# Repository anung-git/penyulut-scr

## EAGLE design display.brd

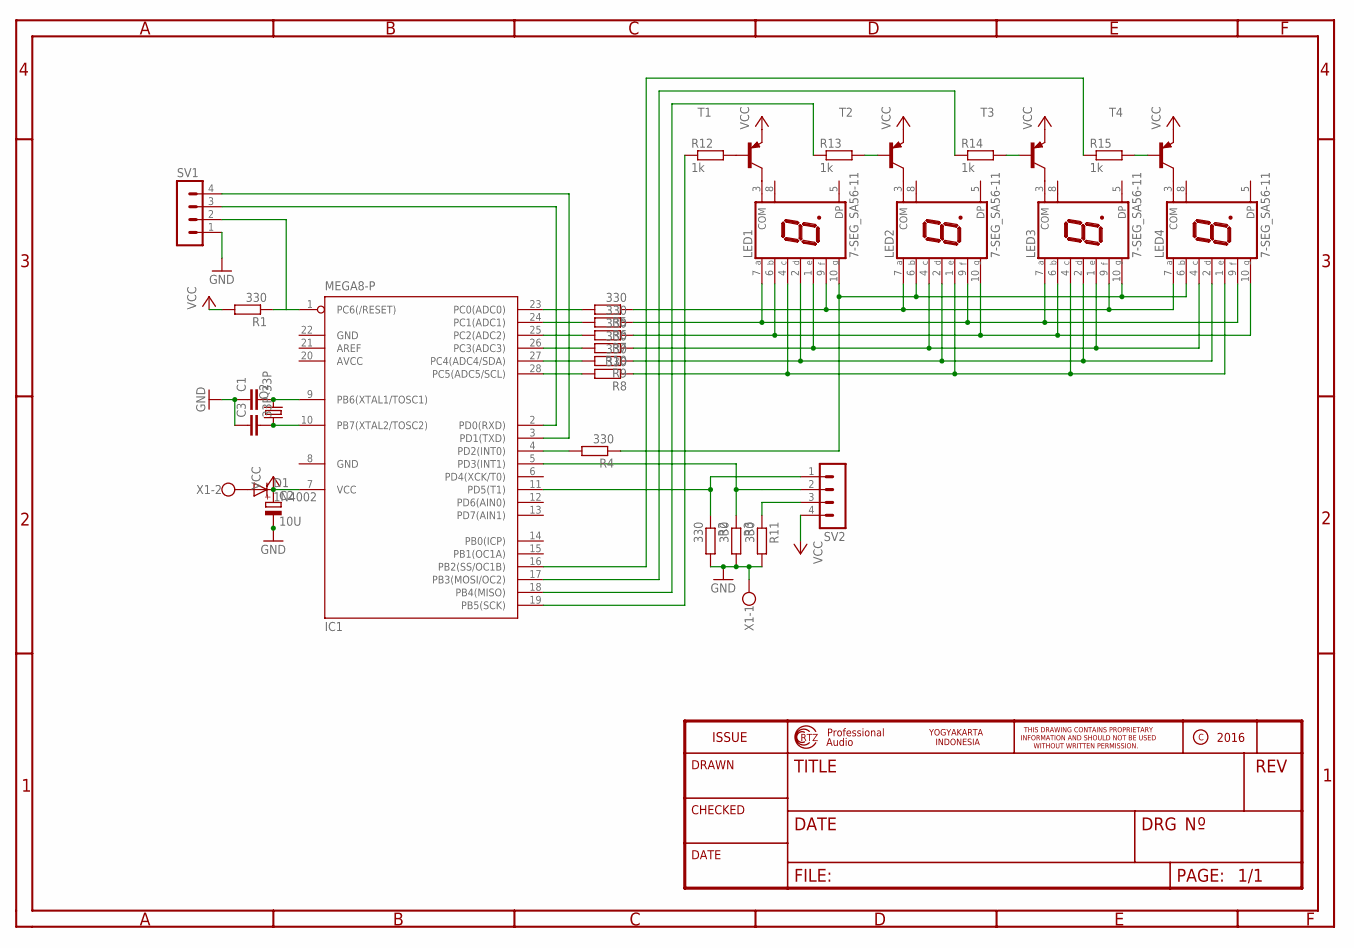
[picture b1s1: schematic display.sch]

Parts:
C1, C3: 33P; C025-025X050
C2: 10U; E2,5-6E
D1: 1N4002; DO35-10
IC1: MEGA8-P; DIL28-3
LED1, LED2, LED3, LED4: 7-SEG_SA56-11; SA56-11
Q2: CRYSTALHC49S; HC49/S
R1, R2, R3, R4, R5, R6, R7, R8, R9, R10, R11: 330; 0207/7
R12, R13, R14, R15: 1k; 0207/7
SV1, SV2: MA04-1
T1, T2, T3, T4: BC558A-PNP-TO92-EBC; TO92-EBC
X1: W237-102

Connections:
AVCC: IC1.20 (AVCC)
GND: C1.1, C2.-, C3.1, IC1.8 (GND), IC1.22 (GND), R2.2, R3.2, R11.2, SV1.1, X1.1
unnamed: IC1.23 (PC0(ADC0)), R5.2
unnamed: LED1.7 (A), LED2.9 (F), LED3.7 (A), LED4.9 (F), R6.1
unnamed: LED1.1 (E), LED2.4 (C), LED3.1 (E), LED4.4 (C), R10.1
unnamed: LED1.2 (D), LED2.2 (D), LED3.2 (D), LED4.2 (D), R9.1
unnamed: LED1.6 (B), LED2.10 (G), LED3.6 (B), LED4.10 (G), R7.1
unnamed: LED1.3 (COM), T1.C
unnamed: LED2.3 (COM), T2.C
unnamed: LED1.4 (C), LED2.1 (E), LED3.4 (C), LED4.1 (E), R8.1
unnamed: C1.2, IC1.9 (PB6(XTAL1/TOSC1)), Q2.2
unnamed: C3.2, IC1.10 (PB7(XTAL2/TOSC2)), Q2.1
unnamed: IC1.2 (PD0(RXD)), SV1.3
unnamed: IC1.24 (PC1(ADC1)), R6.2
unnamed: IC1.1 (PC6(/RESET)), R1.1, SV1.2
unnamed: LED3.3 (COM), T3.C
unnamed: LED4.3 (COM), T4.C
unnamed: IC1.25 (PC2(ADC2)), R7.2
unnamed: IC1.26 (PC3(ADC3)), R10.2
unnamed: IC1.27 (PC4(ADC4/SDA)), R9.2
unnamed: IC1.28 (PC5(ADC5/SCL)), R8.2
unnamed: IC1.4 (PD2(INT0)), R4.2
unnamed: IC1.3 (PD1(TXD)), SV1.4
unnamed: IC1.5 (PD3(INT1)), R3.1, SV2.2
unnamed: R12.2, T1.B
unnamed: R13.2, T2.B
unnamed: R14.2, T3.B
unnamed: LED1.10 (G), LED2.6 (B), LED3.10 (G), LED4.6 (B), R4.1
unnamed: R15.2, T4.B
unnamed: IC1.19 (PB5(SCK)), R12.1
unnamed: IC1.18 (PB4(MISO)), R13.1
unnamed: IC1.17 (PB3(MOSI/OC2)), R14.1
unnamed: IC1.16 (PB2(SS/OC1B)), R15.1
unnamed: IC1.11 (PD5(T1)), R2.1, SV2.1
unnamed: LED1.9 (F), LED2.7 (A), LED3.9 (F), LED4.7 (A), R5.1
unnamed: R11.1, SV2.3
unnamed: D1.A, X1.2
VCC: C2.+, D1.C, IC1.7 (VCC), R1.2, SV2.4, T1.E, T2.E, T3.E, T4.E

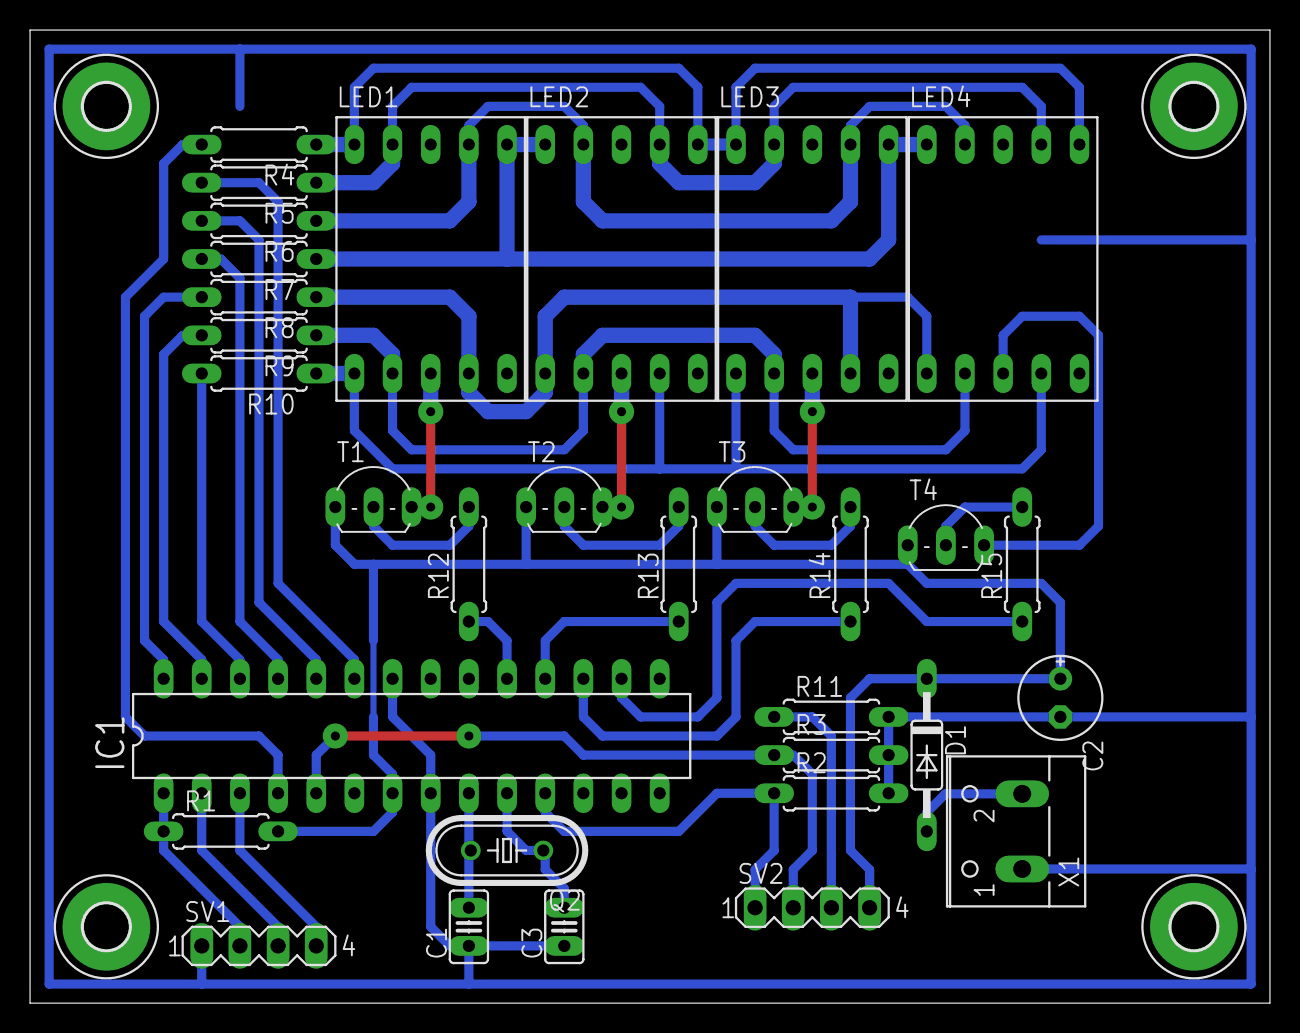
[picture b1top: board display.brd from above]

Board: 2 copper layers, 82.5 x 64.8 mm, 36 parts (0 on the bottom side), 37 nets.

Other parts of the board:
H1, H2, H3, H4: MOUNT-PAD-ROUND3.0; 3,0-PAD

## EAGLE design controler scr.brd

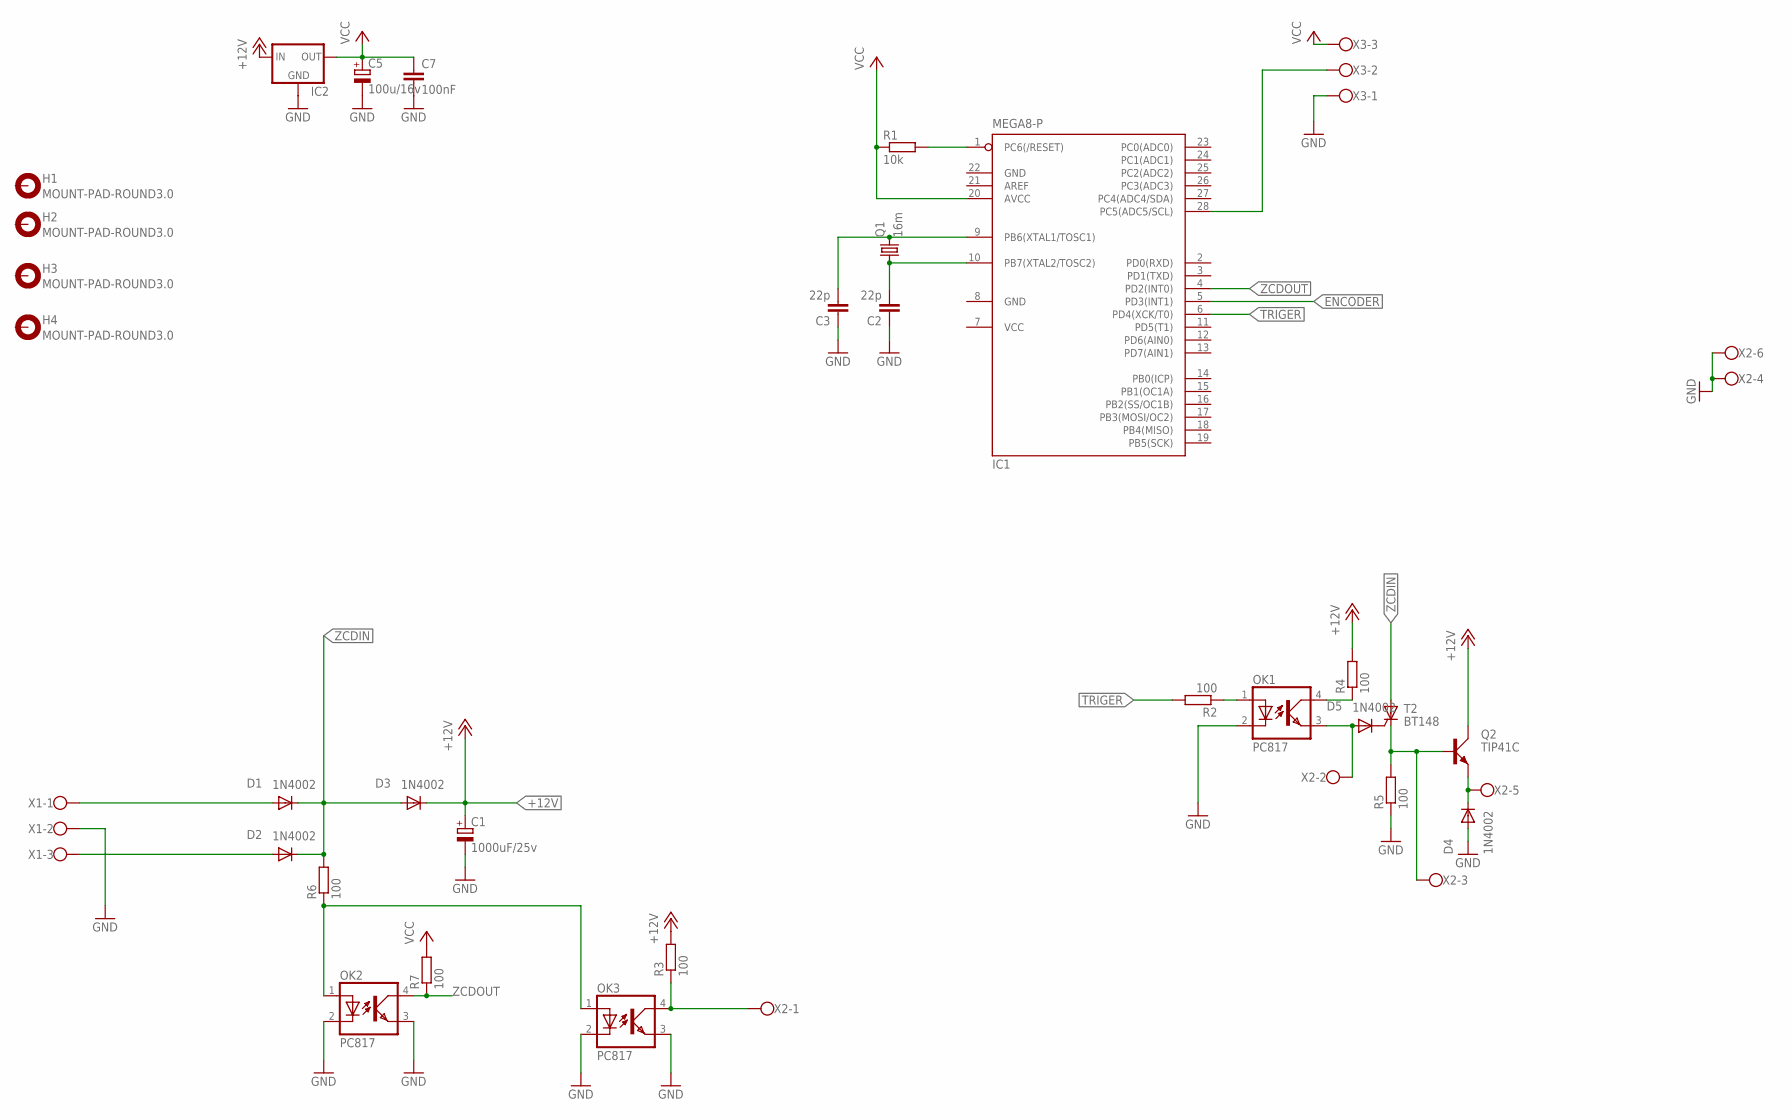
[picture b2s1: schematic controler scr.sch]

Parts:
C1: 1000uF/25v; E5-10,5
C2, C3: 22p; C025-025X050
C5: 100u/16v; E2,5-5
C7: 100nF; C025-025X050
D1, D2, D3, D4, D5: 1N4002; DO35-10
H1, H2, H3, H4: MOUNT-PAD-ROUND3.0; 3,0-PAD
IC1: MEGA8-P; DIL28-3
IC2: 78XXS
OK1, OK2, OK3: PC817; DIL04
Q1: 16m; HC49U-V
Q2: TIP41C; TO220AV
R1: 10k; 0207/10
R2, R3, R4, R5, R6, R7: 100; 0207/10
T2: BT148; SOT82S
X1, X3: W237-103
X2: W237-6

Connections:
+12V: C1.+, D3.C, IC2.IN, Q2.C, R3.2, R4.2
CTA: D1.A, X1.1
CTB: D2.A, X1.3
ENCODER: IC1.5 (PD3(INT1))
GND: C1.-, C2.1, C3.1, C5.-, C7.2, D4.A, IC1.8 (GND), IC1.22 (GND), IC2.GND, OK1.2 (C), OK2.2 (C), OK2.3 (EMIT), OK3.2 (C), OK3.3 (EMIT), R5.1, X1.2, X2.4, X2.6, X3.1
unnamed: IC1.1 (PC6(/RESET)), R1.2
unnamed: IC1.28 (PC5(ADC5/SCL)), X3.2
unnamed: D5.C, T2.G
unnamed: OK2.1 (A), OK3.1 (A), R6.1
unnamed: D4.C, Q2.E, X2.5
unnamed: C3.2, IC1.9 (PB6(XTAL1/TOSC1)), Q1.2
unnamed: OK3.4 (COL), R3.1, X2.1
unnamed: C2.2, IC1.10 (PB7(XTAL2/TOSC2)), Q1.1
unnamed: D5.A, OK1.3 (EMIT), X2.2
unnamed: OK1.4 (COL), R4.1
unnamed: Q2.B, R5.2, T2.C, X2.3
unnamed: OK1.1 (A), R2.1
TRIGER: IC1.6 (PD4(XCK/T0)), R2.2
VCC: C5.+, C7.1, IC1.7 (VCC), IC1.20 (AVCC), IC2.OUT, R1.1, R7.2, X3.3
ZCDIN: D1.C, D2.C, D3.A, R6.2, T2.A
ZCDOUT: IC1.4 (PD2(INT0)), OK2.4 (COL), R7.1

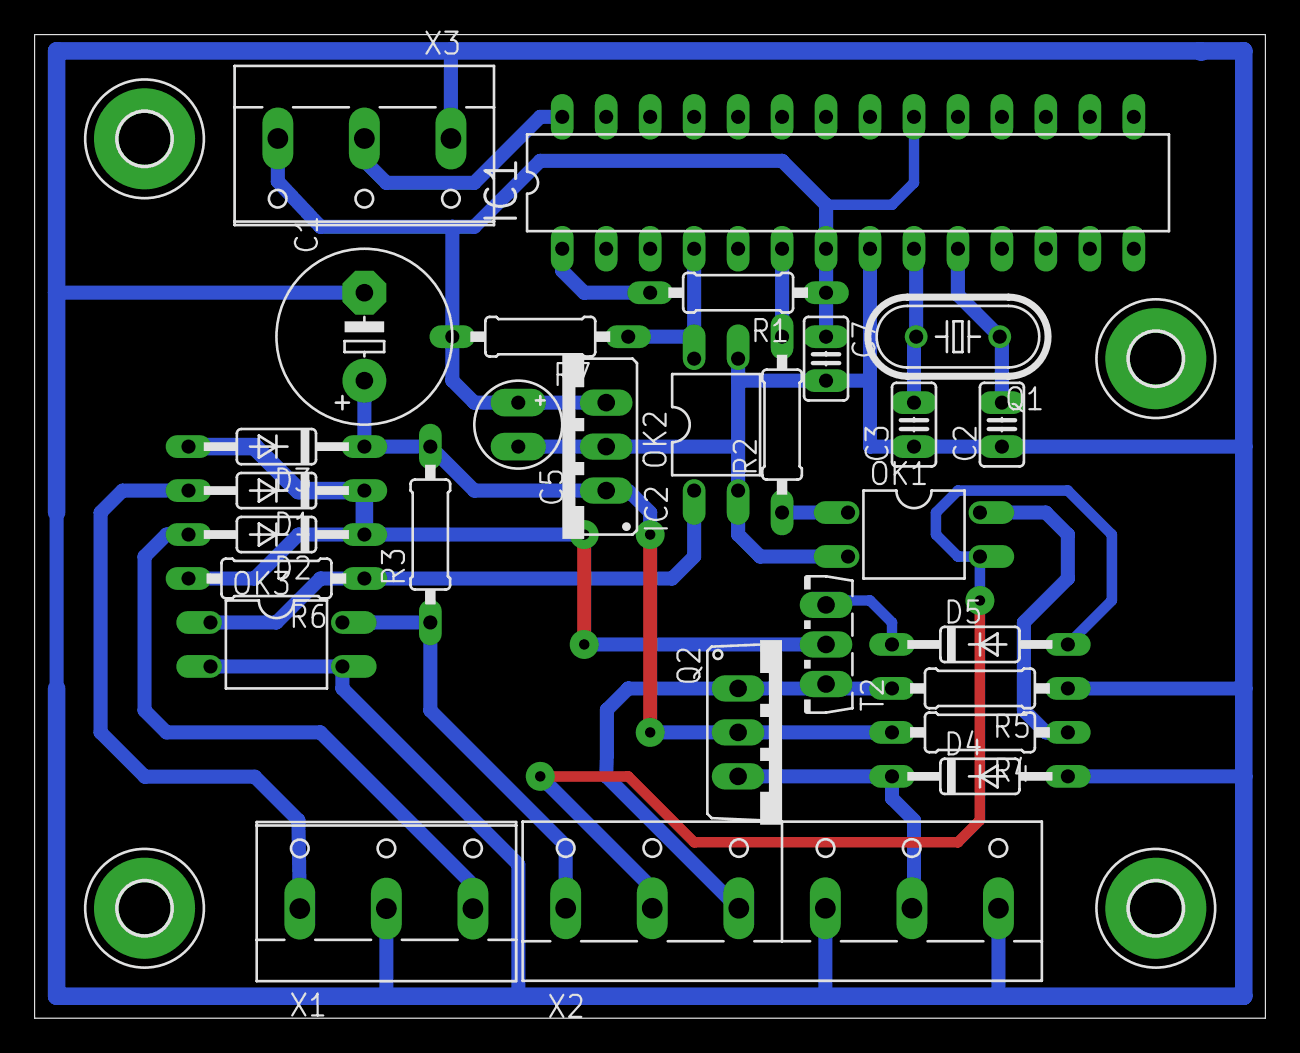
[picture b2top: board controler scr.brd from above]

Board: 2 copper layers, 71.1 x 56.8 mm, 32 parts (0 on the bottom side), 20 nets.

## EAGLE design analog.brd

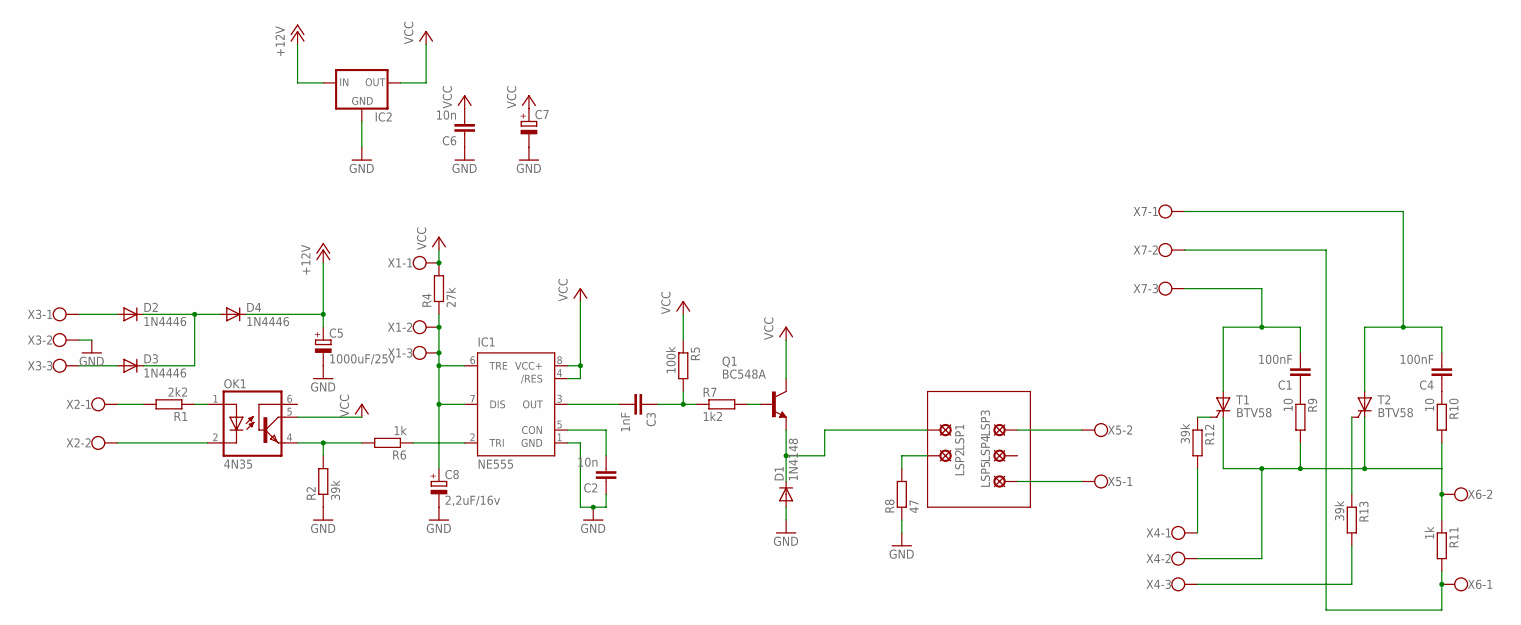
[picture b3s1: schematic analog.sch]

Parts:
C1, C4: 100nF; C050-025X075
C2, C6: 10n; C050-025X075
C3: 1nF; C050-025X075
C5: 1000uF/25v; E5-8,5
C7: CPOL-EUE2.5-5; E2,5-5
C8: 2,2uF/16v; E2,5-5
D1: 1N4148; DO35-10
D2, D3, D4: 1N4446; DO35-10
IC1: NE555; DIL-08
IC2: 78XXS
LSP1, LSP2, LSP3, LSP4, LSP5: MCS10B
OK1: 4N35; DIL06
Q1: BC548A; TO92-EBC
R1: 2k2; 0207/10
R2, R12, R13: 39k; 0207/10
R4: 27k; 0207/10
R5: 100k; 0207/10
R6, R11: 1k; 0207/10
R7: 1k2; 0207/10
R8: 47; 0207/10
R9, R10: 10; 0207/10
T1, T2: BTV58; TO220CS
X1, X3, X4, X7: W237-103
X2, X5, X6: W237-102

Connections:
+12V: C5.+, D4.C, IC2.IN
GND: C2.1, C5.-, C6.1, C7.-, C8.-, D1.A, IC1.1 (GND), IC2.GND, R2.1, R8.1, X3.2
unnamed: OK1.1 (A), R1.1
unnamed: OK1.4 (EMI), R2.2, R6.2
unnamed: C2.2, IC1.5 (CON)
unnamed: IC1.2 (TRI), R6.1
unnamed: C8.+, IC1.6 (TRE), IC1.7 (DIS), R4.1, X1.2, X1.3
unnamed: C3.1, R5.2, R7.1
unnamed: C3.2, IC1.3 (OUT)
unnamed: Q1.B, R7.2
unnamed: D1.C, LSP1.MP, Q1.E
unnamed: D2.C, D3.C, D4.A
unnamed: R1.2, X2.1
unnamed: D2.A, X3.1
unnamed: D3.A, X3.3
unnamed: OK1.2 (C), X2.2
unnamed: LSP2.MP, R8.2
unnamed: R12.2, X4.1
unnamed: LSP3.MP, X5.2
unnamed: LSP5.MP, X5.1
unnamed: C1.1, R9.1
unnamed: C1.2, T1.A, X7.3
unnamed: R11.2, X6.1, X7.2
unnamed: C4.1, R10.1
unnamed: C4.2, T2.A, X7.1
unnamed: R13.2, X4.3
unnamed: R12.1, T1.G
unnamed: R13.1, T2.G
unnamed: R9.2, R10.2, R11.1, T1.C, T2.C, X4.2, X6.2
VCC: C6.2, C7.+, IC1.4 (/RES), IC1.8 (VCC+), IC2.OUT, OK1.5 (COL), Q1.C, R4.2, R5.1, X1.1

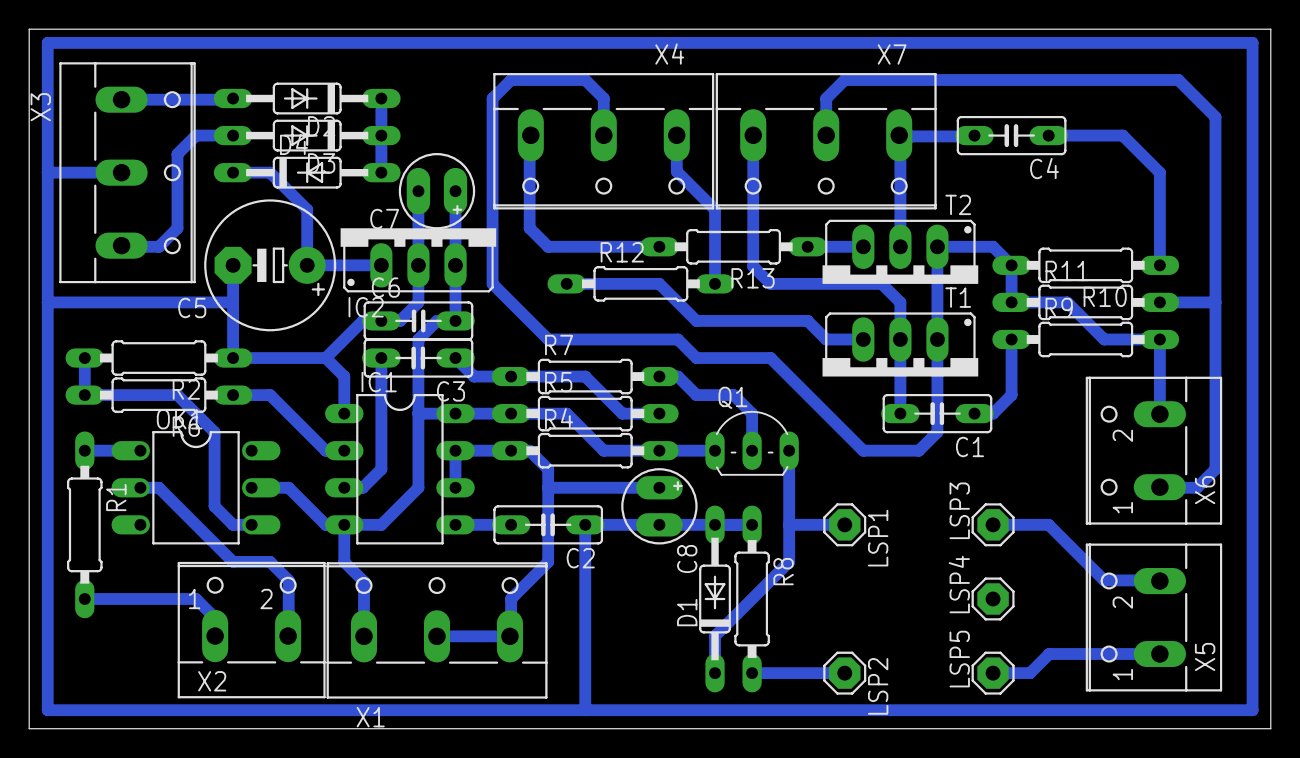
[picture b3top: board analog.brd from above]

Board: 2 copper layers, 85.1 x 47.9 mm, 42 parts (0 on the bottom side), 30 nets.

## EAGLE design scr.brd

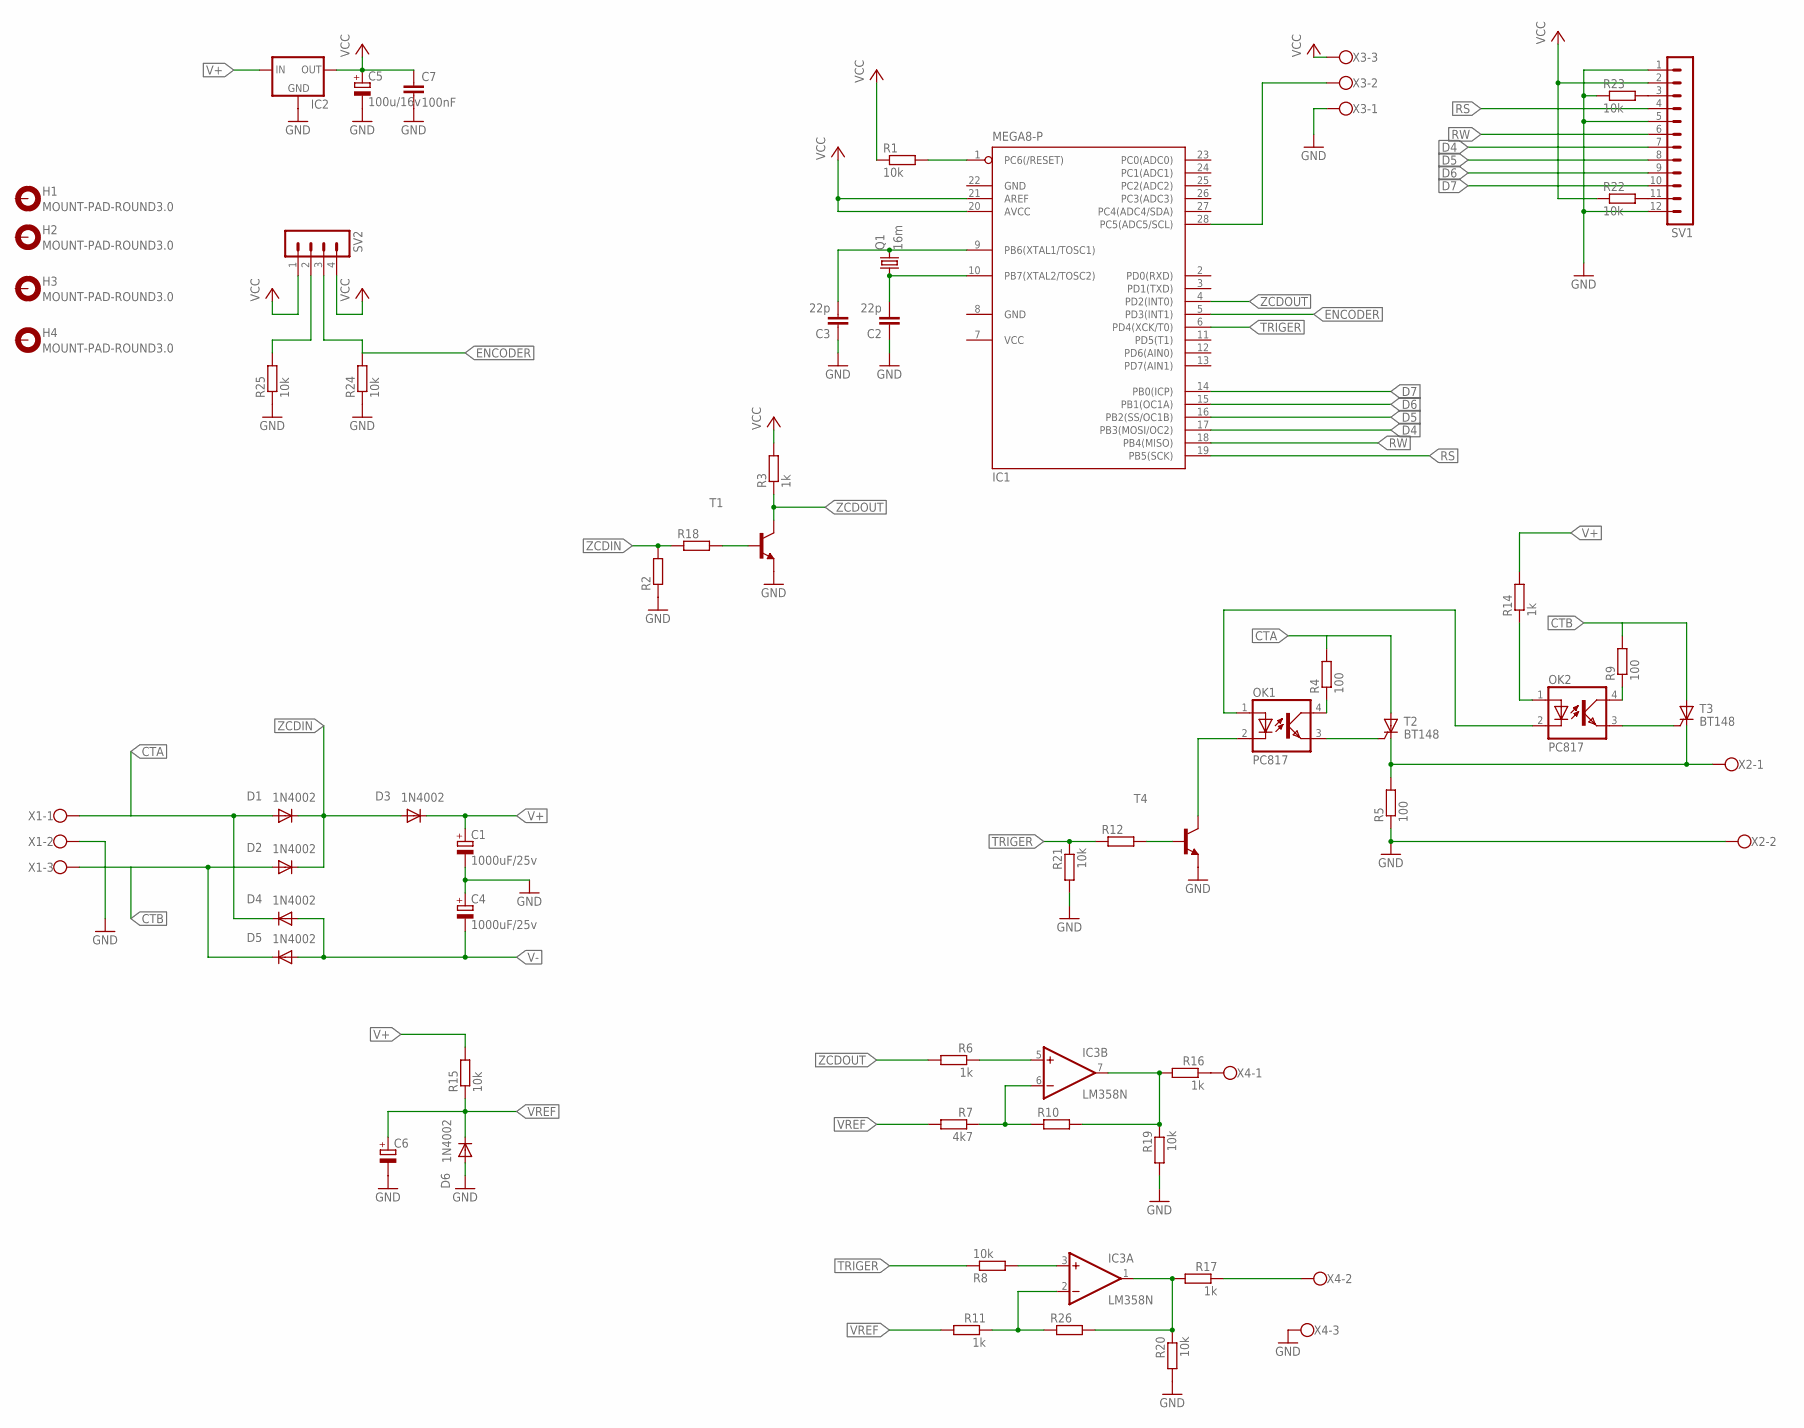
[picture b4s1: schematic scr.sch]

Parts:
C1, C4: 1000uF/25v; E5-10,5
C2, C3: 22p; C025-025X050
C5: 100u/16v; E2,5-5
C6: CPOL-EUE2.5-5; E2,5-5
C7: 100nF; C025-025X050
D1, D2, D3, D4, D5, D6: 1N4002; DO35-10
H1, H2, H3, H4: MOUNT-PAD-ROUND3.0; 3,0-PAD
IC1: MEGA8-P; DIL28-3
IC2: 78XXS
IC3: LM358N; DIL08
OK1, OK2: PC817; DIL04
Q1: 16m; HC49U-V
R1, R8, R15, R19, R20, R21, R22, R23, R24, R25: 10k; 0207/10
R2, R10, R12, R18, R26: R-EU_0207/2V; 0207/2V
R3, R6, R11, R14, R16, R17: 1k; 0207/10
R4, R5, R9: 100; 0207/10
R7: 4k7; 0207/10
SV1: MA12-1
SV2: MA04-1
T1, T4: BC337-NPN-TO92-CBE; TO92-CBE
T2, T3: BT148; SOT82S
X1, X3, X4: W237-103
X2: W237-102

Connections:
CTA: D1.A, D4.C, R4.2, T2.A, X1.1
CTB: D2.A, D5.C, R9.2, T3.A, X1.3
D4: IC1.17 (PB3(MOSI/OC2)), SV1.7
D5: IC1.16 (PB2(SS/OC1B)), SV1.8
D6: IC1.15 (PB1(OC1A)), SV1.9
D7: IC1.14 (PB0(ICP)), SV1.10
ENCODER: IC1.5 (PD3(INT1)), R24.2, SV2.3
GND: C1.-, C2.1, C3.1, C4.+, C5.-, C6.-, C7.2, D6.A, IC1.8 (GND), IC1.22 (GND), IC2.GND, R2.1, R5.1, R19.2, R20.2, R21.2, R23.1, R24.1, R25.1, SV1.1, SV1.5, SV1.12, T1.E, T4.E, X1.2, X2.2, X3.1, X4.3
unnamed: IC1.1 (PC6(/RESET)), R1.2
unnamed: IC1.28 (PC5(ADC5/SCL)), X3.2
unnamed: R18.2, T1.B
unnamed: R22.2, SV1.11
unnamed: R23.2, SV1.3
unnamed: C3.2, IC1.9 (PB6(XTAL1/TOSC1)), Q1.2
unnamed: IC3.3 (+IN), R8.2
unnamed: C2.2, IC1.10 (PB7(XTAL2/TOSC2)), Q1.1
unnamed: OK1.3 (EMIT), T2.G
unnamed: OK1.4 (COL), R4.1
unnamed: IC3.2 (-IN), R11.1, R26.1
unnamed: IC3.1 (OUT), R17.2, R20.1, R26.2
unnamed: R25.2, SV2.2
unnamed: IC3.5 (+IN), R6.1
unnamed: IC3.6 (-IN), R7.1, R10.1
unnamed: IC3.7 (OUT), R10.2, R16.2, R19.1
unnamed: OK2.3 (EMIT), T3.G
unnamed: OK2.4 (COL), R9.1
unnamed: OK2.1 (A), R14.1
unnamed: R5.2, T2.C, T3.C, X2.1
unnamed: OK1.1 (A), OK2.2 (C)
unnamed: R12.2, T4.B
unnamed: R16.1, X4.1
unnamed: OK1.2 (C), T4.C
unnamed: R17.1, X4.2
RS: IC1.19 (PB5(SCK)), SV1.4
RW: IC1.18 (PB4(MISO)), SV1.6
TRIGER: IC1.6 (PD4(XCK/T0)), R8.1, R12.1, R21.1
V+: C1.+, D3.C, IC2.IN, IC3.8 (V+), R14.2, R15.2
V-: C4.-, D4.A, D5.A, IC3.4 (V-)
VCC: C5.+, C7.1, IC1.7 (VCC), IC1.20 (AVCC), IC1.21 (AREF), IC2.OUT, R1.1, R3.2, R22.1, SV1.2, SV2.1, SV2.4, X3.3
VREF: C6.+, D6.C, R7.2, R11.2, R15.1
ZCDIN: D1.C, D2.C, D3.A, R2.2, R18.1
ZCDOUT: IC1.4 (PD2(INT0)), R3.1, R6.2, T1.C

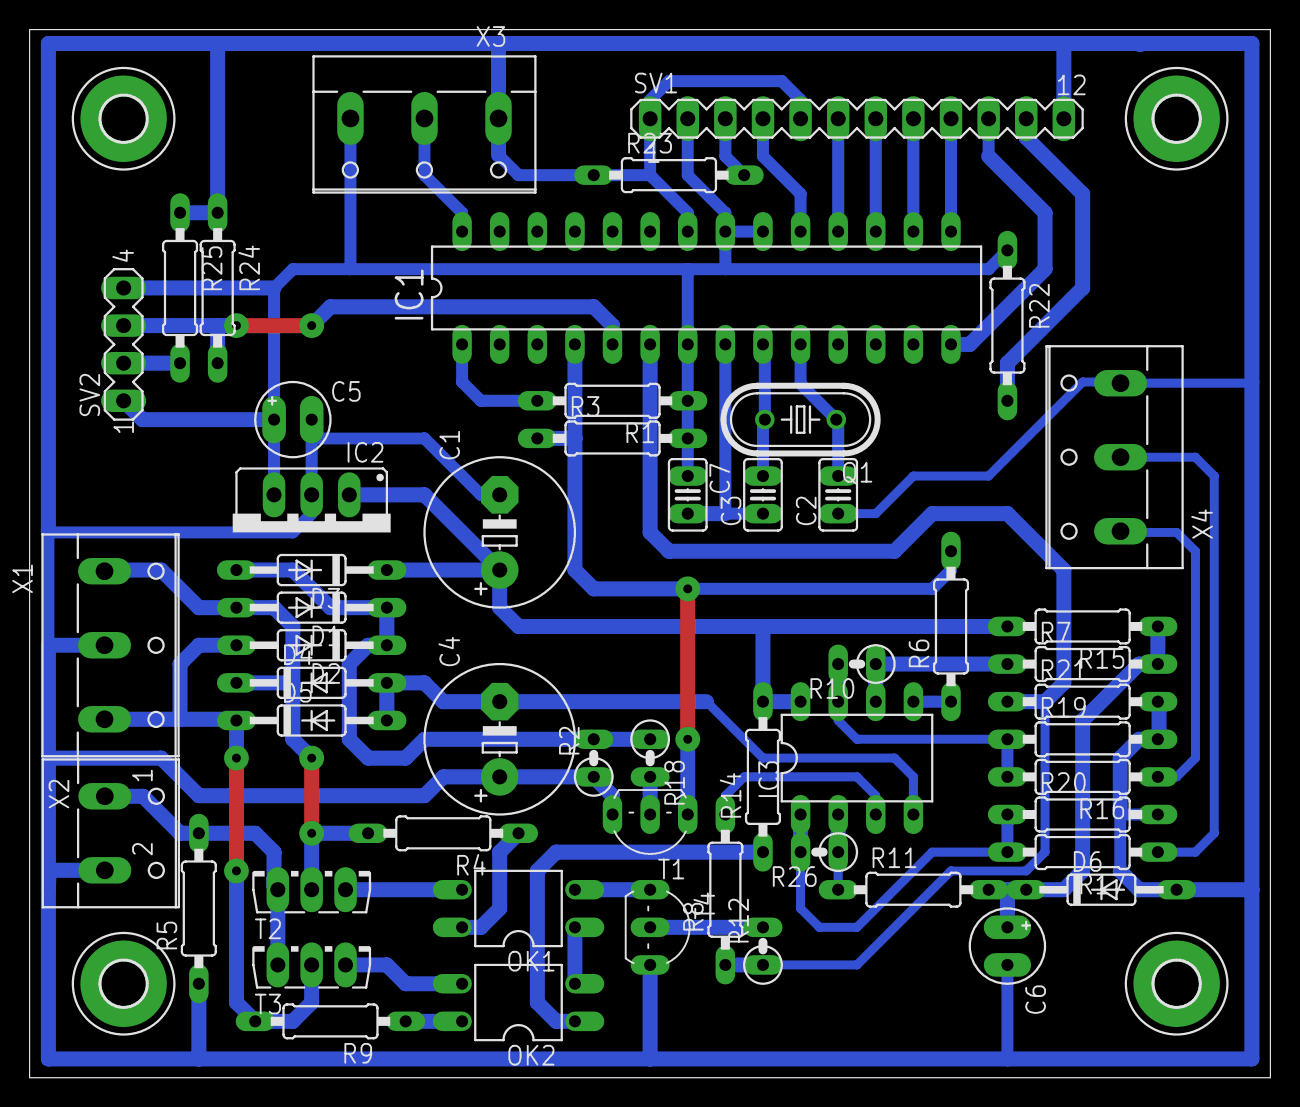
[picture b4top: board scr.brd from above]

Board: 2 copper layers, 83.8 x 70.8 mm, 58 parts (0 on the bottom side), 42 nets.

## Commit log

2019-08-26 uload
2019-08-26 upload
2019-08-26 hapus
2019-08-26 edit
2019-08-26 lanjutkan
2019-08-26 rampung
2019-08-26 lagi
2019-08-27 finish
2019-08-28 geser dioda
2019-09-01 tambah program arduino
2019-09-01 compile
2019-09-01 simulasikan
2019-09-03 comment fungsi gateOn
2019-09-05 hapus lib timerone
2019-09-08 adjust timer
2019-09-09 tambah upload linux
2019-09-10 tambah manual
2019-09-10 rout
2019-09-11 finish sch
2019-09-12 routing
2019-09-15 tambah progam bascom
2019-09-21 tambah pcb controler
2019-09-21 rubah digitalWrite
2019-09-21 tambah pcb display 7 segment
2019-09-29 tambah program tacometer
2019-09-29 hapus inisialisasi port
2019-11-05 tambah skema
2019-11-05 UPDATE skema
2019-11-05 tambah pot
2019-11-05 rotate value resistor
2019-11-08 edit acrilic
2019-11-16 resize
2019-11-17 revisi
2019-11-17 delete
2019-11-19 reset eagle
2019-11-19 edit controler
2020-01-04 reset display

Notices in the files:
parts and their libraries:
dframes - Copy: Copyright (C) 2004, Bob Starr (bobstarr@mindspring.com)
